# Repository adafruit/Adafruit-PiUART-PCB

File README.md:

## Adafruit PiUART PCB

<a href="http://www.adafruit.com/products/3589"><br/>
Click here to purchase one from the Adafruit shop</a>

PCB files for the Adafruit PiUART PCB. Format is EagleCAD schematic and board layout

For more details, check out the product page at
* http://www.adafruit.com/product/3589

### Description

Here's another super handy add-on for your Raspberry Pi computer, perfect for 'head-less' setups! The PiUART adds a USB Type-C to serial connection so you can use any serial port software to connect to the Pi's console. It plugs in and is fast and easy to add whenever you need to connect to your Pi. Two LEDs connect to RX and TX on the serial converter chip so you get blinking whenever data is sent or received..

We had some space left over, so the PiUART also comes with an on-off switch with a 4 Amp transistor. You can power your Pi through the USB-C port and then use the switch whenever you want to cut power, without having to unplug the cable. Low-power usage Pi's like the Pi Zero and A+ can thus be powered and controlled from a single cable connected to your computer. Heavy-hitter Pi's like the Pi 2 and Pi 3 may draw too much power from a computer USB port, so check if your motherboard has a high-current USB port before trying.

Comes fully assembled and ready to go, plug into your Pi, and on Mac OS X install the driver - within 2 minutes and you'll be ready to go.

Works with any Raspberry Pi computer (Pi 1, 2, 3, Zero, etc)

### License

Adafruit invests time and resources providing this open source design, please support Adafruit and open-source hardware by purchasing products from [Adafruit](https://www.adafruit.com)!

Designed by Limor Fried/Ladyada for Adafruit Industries.

Creative Commons Attribution/Share-Alike, all text above must be included in any redistribution. See license.txt for additional details.

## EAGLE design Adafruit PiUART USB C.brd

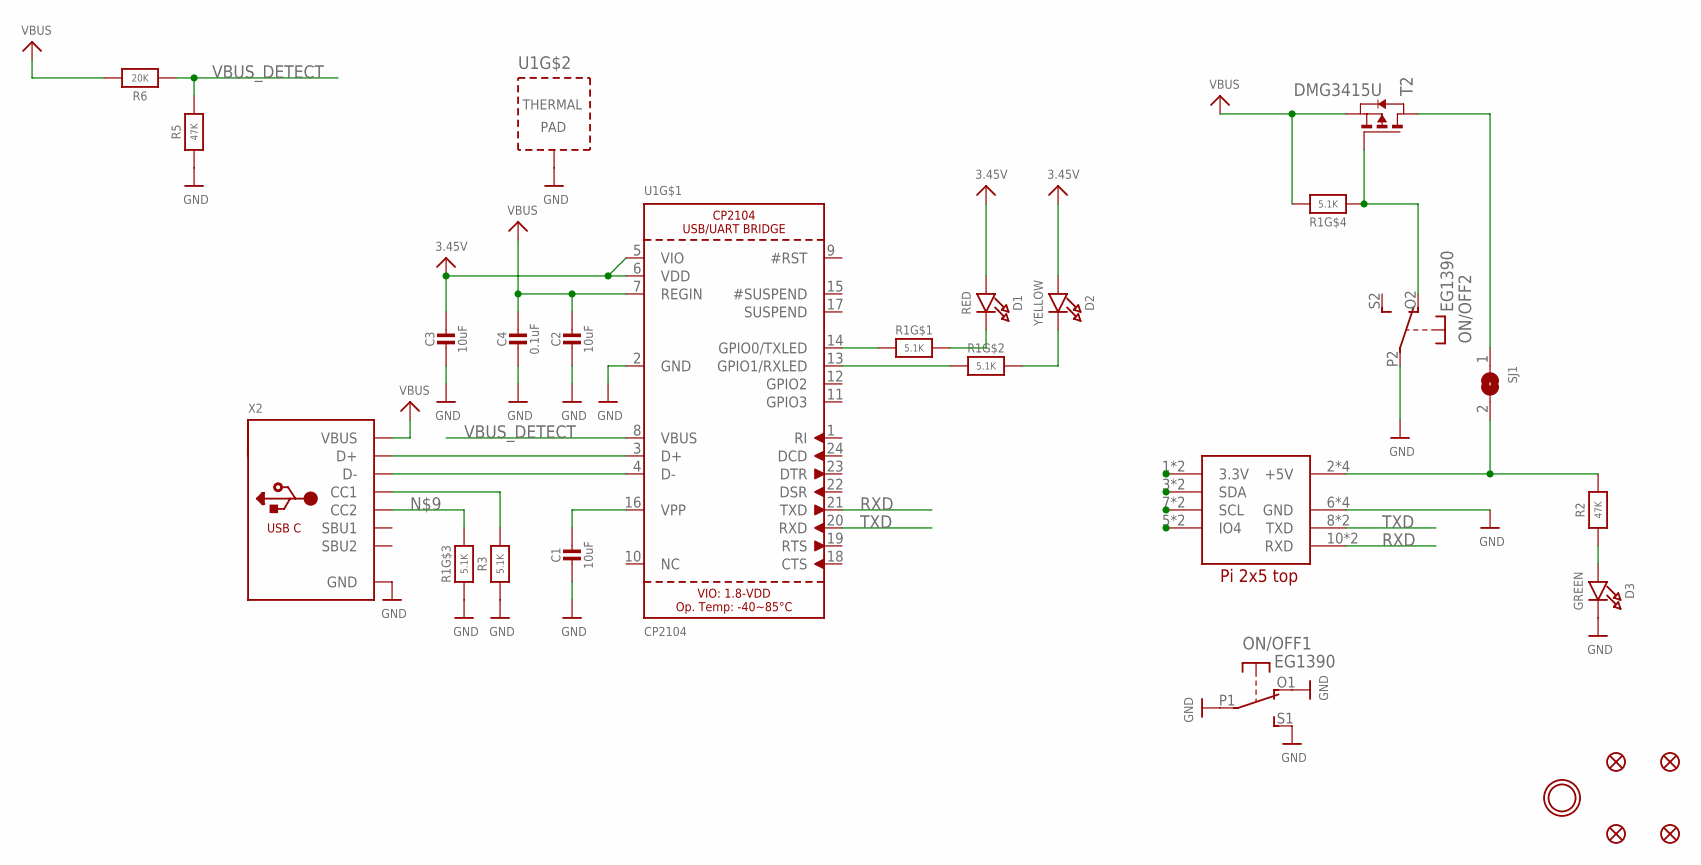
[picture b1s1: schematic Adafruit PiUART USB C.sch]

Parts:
C1, C2, C3: 10uF; 0805-NO
C4: 0.1uF; 0603-NO
D1: RED; CHIPLED_0603_NOOUTLINE
D2: YELLOW; CHIPLED_0603_NOOUTLINE
D3: GREEN; CHIPLED_0603_NOOUTLINE
FID1, FID2, FID3, FID4: FIDUCIAL_1MM
ON/OFF: EG1390
R1: 5.1K; RESPACK_4X0603
R2, R5: 47K; 0603-NO
R3: 5.1K; 0603-NO
R6: 20K; 0603-NO
SJ1: SOLDERJUMPERCLOSED; SOLDERJUMPER_CLOSEDWIRE
T2: DMG3415U; SOT-23
U1: CP2104; QFN24_4MM_SMSC
U$9: RASPBERRYPI_2X5; RASPBERRYPI_2X5_THMSMT
U$18: MOUNTINGHOLE3.0THIN; MOUNTINGHOLE_3.0_PLATEDTHIN
X2: USB_C; USB_C_CUSB31-CFM2AX-01-X

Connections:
3.3V: C3.1, D1.A, D2.A, U1.5 (VIO), U1.6 (VDD)
5V: R2.2, SJ1.2, U$9.2 (+5V), U$9.2' (+5V), U$9.4 (+5V), U$9.4' (+5V)
GND: C1.2, C2.2, C3.2, C4.2, D3.C, ON/OFF.O1 (O), ON/OFF.P1, ON/OFF.P2, ON/OFF.S1 (S), R1.3 (1), R3.1, R5.1, U1.2 (GND), U1.THERM (TP), U$9.6 (GND), U$9.6' (GND), U$9.9 (GND), U$9.9' (GND), X2.A1B12 (GND), X2.B1A12 (GND)
unnamed: D3.A, R2.1
unnamed: U1.3 (D+), X2.A6 (D+), X2.B6 (D+)
unnamed: U1.4 (D-), X2.A7 (D-), X2.B7 (D-)
unnamed: C1.1, U1.16 (VPP)
unnamed: R1.1, U1.14 (GPIO0/TXLED)
unnamed: D1.C, R1.8 (2)
unnamed: R1.2 (1), U1.13 (GPIO1/RXLED)
unnamed: D2.C, R1.7 (2)
unnamed: R1.6 (2), X2.B5 (CC2)
unnamed: R3.2, X2.A5 (CC1)
unnamed: ON/OFF.O2 (O), R1.4 (1), T2.3 (G)
NC1: U$9.1 (3.3V), U$9.1' (3.3V)
NC2: U$9.3 (SDA), U$9.3' (SDA)
NC3: U$9.5 (IO4), U$9.5' (IO4)
NC4: U$9.7 (SCL), U$9.7' (SCL)
RXD: U1.21 (TXD), U$9.10 (RXD), U$9.10' (RXD)
TXD: U1.20 (RXD), U$9.8 (TXD), U$9.8' (TXD)
VBUS: C2.1, C4.1, R1.5 (2), R6.2, T2.2 (S), U1.7 (REGIN), X2.A4B9 (VBUS), X2.B4A9 (VBUS)
VBUS_DETECT: R5.2, R6.1, U1.8 (VBUS)
VIN: SJ1.1, T2.1 (D)

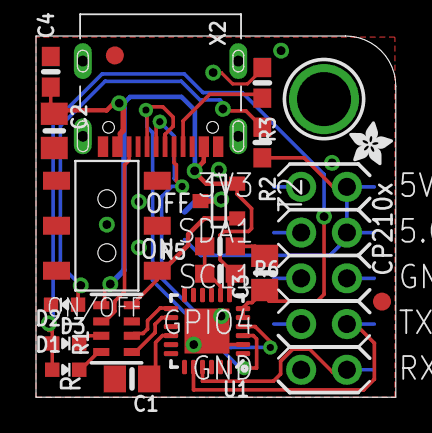
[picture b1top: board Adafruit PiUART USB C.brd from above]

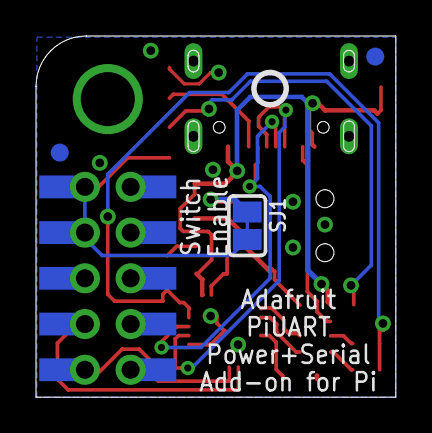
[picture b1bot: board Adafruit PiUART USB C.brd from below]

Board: 2 copper layers, 20.0 x 20.1 mm, 25 parts (4 on the bottom side), 23 nets.

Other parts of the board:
U$8: ADAFRUIT_2.5MM
U$17: PCBFEAT-REV-040

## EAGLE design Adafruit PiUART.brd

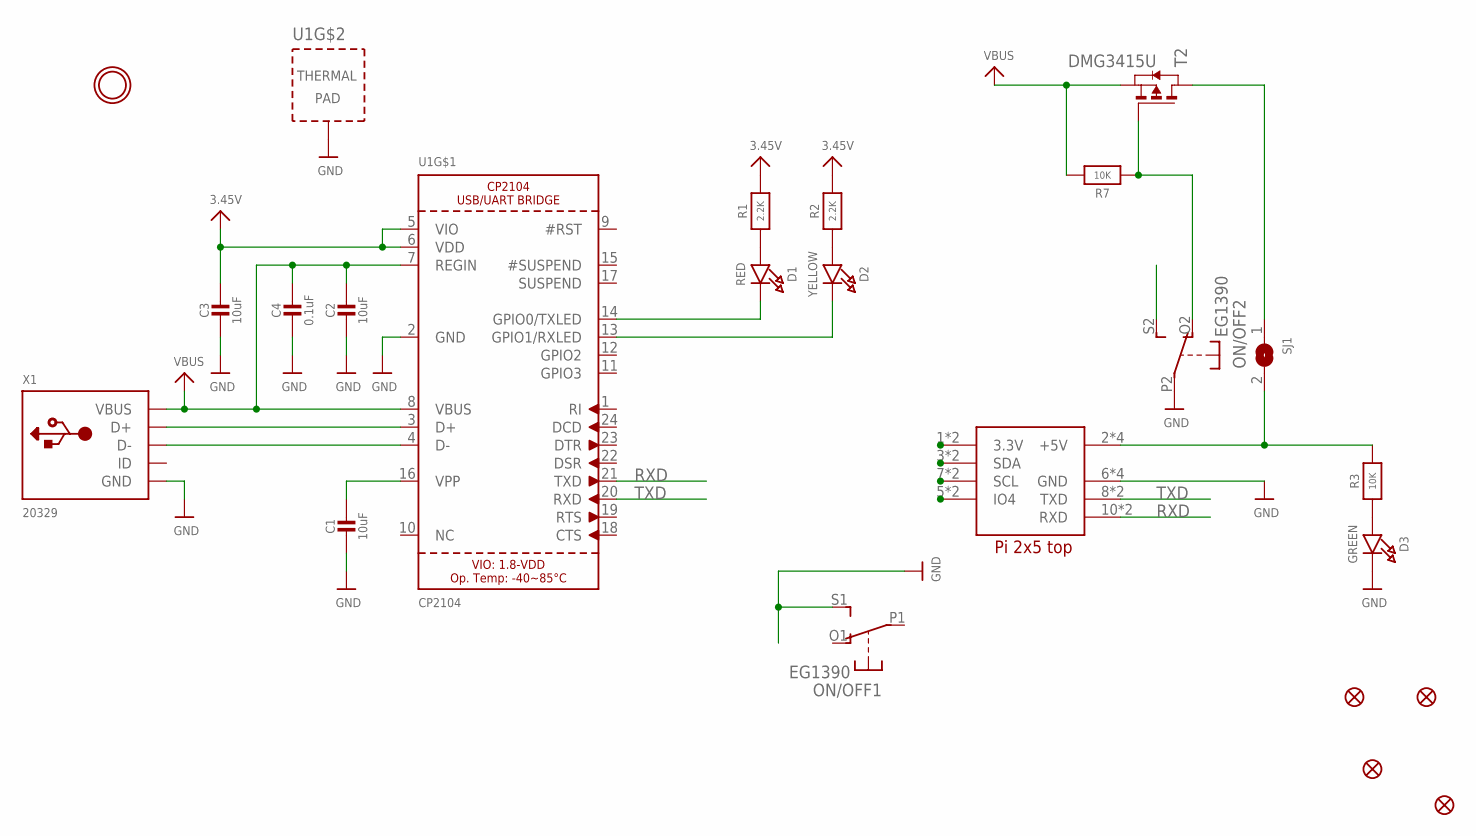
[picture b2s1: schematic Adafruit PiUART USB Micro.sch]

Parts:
C1, C2, C3: 10uF; 0805-NO
C4: 0.1uF; 0603-NO
D1: RED; CHIPLED_0603_NOOUTLINE
D2: YELLOW; CHIPLED_0603_NOOUTLINE
D3: GREEN; CHIPLED_0603_NOOUTLINE
FID1, FID2, FID3, FID4: FIDUCIAL_1MM
ON/OFF: EG1390
R1, R2: 2.2K; 0603-NO
R3, R7: 10K; 0603-NO
SJ1: SOLDERJUMPERCLOSED; SOLDERJUMPER_CLOSEDWIRE
T2: DMG3415U; SOT-23
U1: CP2104; QFN24_4MM_SMSC
U$9: RASPBERRYPI_2X5; RASPBERRYPI_2X5_THMSMT
U$18: MOUNTINGHOLE3.0THIN; MOUNTINGHOLE_3.0_PLATEDTHIN
X1: 20329; 4UCONN_20329_V2

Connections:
3.3V: C3.1, R1.2, R2.2, U1.5 (VIO), U1.6 (VDD)
GND: C1.2, C2.2, C3.2, C4.2, D3.C, ON/OFF.P2, ON/OFF.S1 (S), U1.2 (GND), U1.THERM (TP), U$9.6 (GND), U$9.6' (GND), U$9.9 (GND), U$9.9' (GND), X1.BASE@1 (GND), X1.BASE@2 (GND), X1.GND, X1.SPRT@1 (GND), X1.SPRT@2 (GND), X1.SPRT@3 (GND), X1.SPRT@4 (GND)
unnamed: D1.A, R1.1
unnamed: U1.3 (D+), X1.D+
unnamed: U1.4 (D-), X1.D-
unnamed: C1.1, U1.16 (VPP)
unnamed: D2.A, R2.1
unnamed: D1.C, U1.14 (GPIO0/TXLED)
unnamed: D2.C, U1.13 (GPIO1/RXLED)
unnamed: U$9.1 (3.3V), U$9.1' (3.3V)
unnamed: U$9.3 (SDA), U$9.3' (SDA)
unnamed: U$9.7 (SCL), U$9.7' (SCL)
unnamed: U$9.5 (IO4), U$9.5' (IO4)
unnamed: R3.2, SJ1.2, U$9.2 (+5V), U$9.2' (+5V), U$9.4 (+5V), U$9.4' (+5V)
unnamed: ON/OFF.O2 (O), R7.1, T2.3 (G)
unnamed: D3.A, R3.1
RXD: U1.21 (TXD), U$9.10 (RXD), U$9.10' (RXD)
TXD: U1.20 (RXD), U$9.8 (TXD), U$9.8' (TXD)
VBUS: C2.1, C4.1, R7.2, T2.2 (S), U1.7 (REGIN), U1.8 (VBUS), X1.VBUS
VIN: SJ1.1, T2.1 (D)

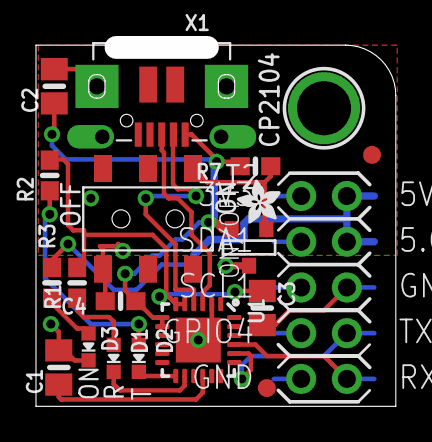
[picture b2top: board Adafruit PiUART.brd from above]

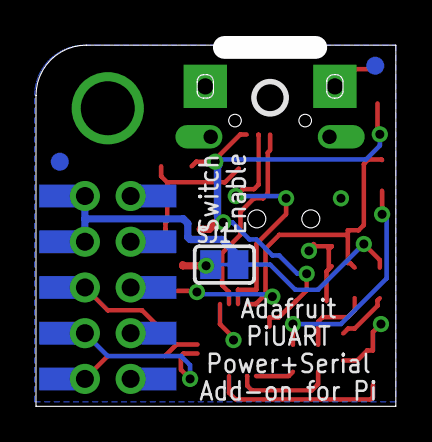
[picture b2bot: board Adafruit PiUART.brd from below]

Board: 2 copper layers, 20.0 x 20.1 mm, 24 parts (4 on the bottom side), 20 nets.

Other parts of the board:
U$8: ADAFRUIT_2.5MM
U$17: PCBFEAT-REV-040

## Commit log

2017-08-29 kpow
2022-04-13 Update board files.

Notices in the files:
parts and their libraries:
microbuilder: This work is placed in the public domain, and may be freely used for commercial and non-commercial work with the following conditions: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
